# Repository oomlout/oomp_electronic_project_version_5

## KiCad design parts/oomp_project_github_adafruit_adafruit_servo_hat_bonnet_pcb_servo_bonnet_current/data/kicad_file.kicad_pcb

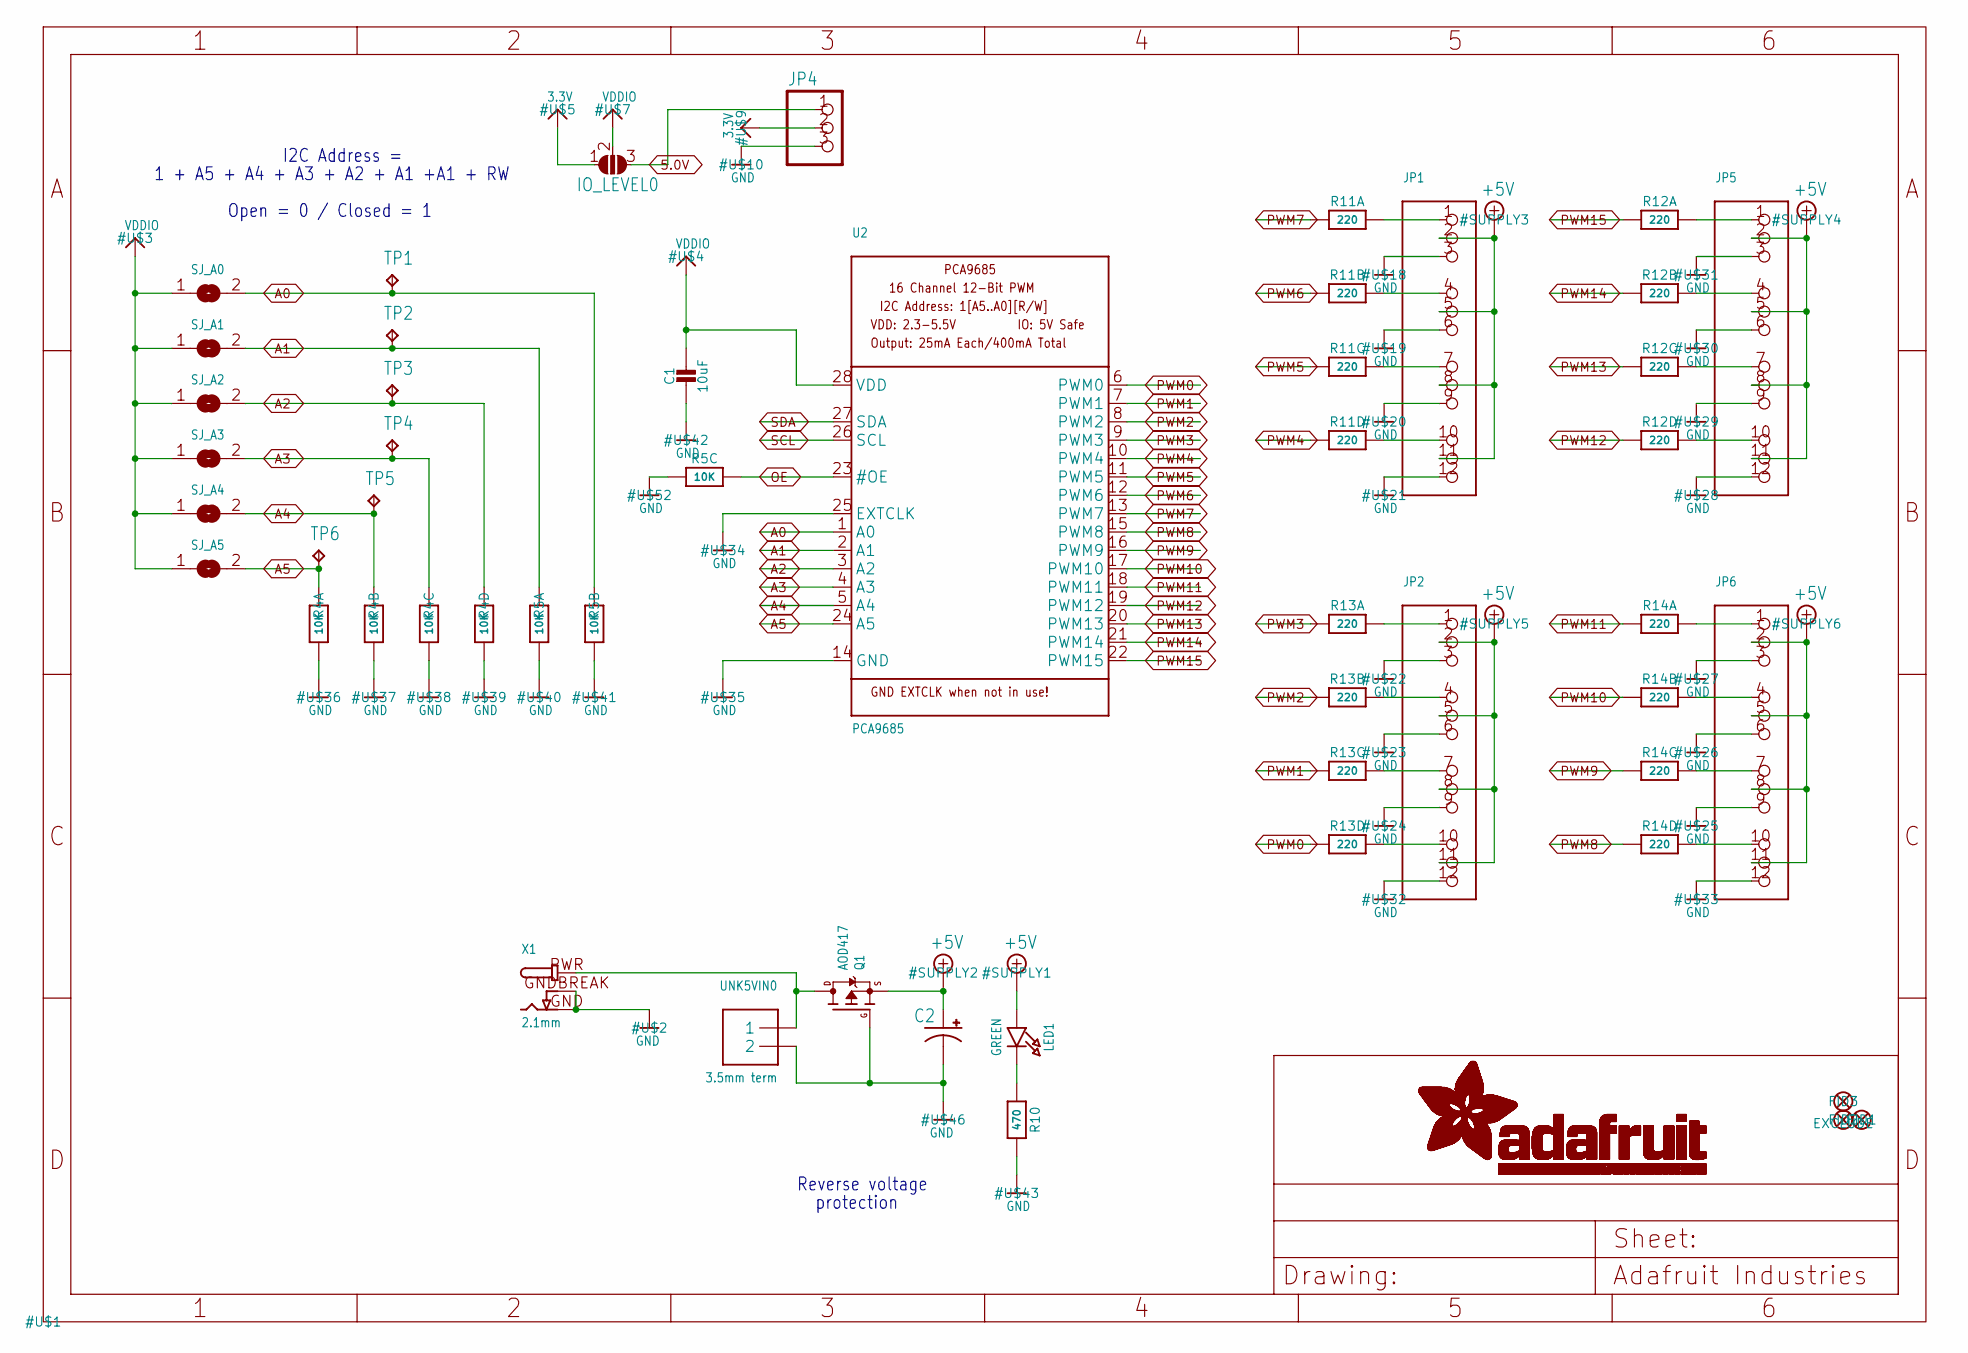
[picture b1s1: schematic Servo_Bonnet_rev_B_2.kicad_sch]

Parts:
C1: 10uF; 0805-NO
C2: CPOL-USE3.5-8; E3,5-8
FID1, FID2, FID3: FIDUCIAL_1MM
IO_LEVEL0: SOLDERJUMPER_2WAY; SOLDERJUMPER_2WAY_OPEN_NOPASTE
JP1, JP2, JP5, JP6: HEADER-3X04; 3X04
JP4: HEADER-1X3ROUND; 1X03_ROUND
LED1: GREEN; CHIPLED_0805_NOOUTLINE
Q1: AOD417; TO252
R4, R5: 10K; RESPACK_4X0603
R10: 470; 0603-NO
R11, R12, R13, R14: 220; RESPACK_4X0603
SJ_A0, SJ_A1, SJ_A2, SJ_A3, SJ_A4, SJ_A5: SOLDERJUMPERREFLOW_NOPASTE; SOLDERJUMPER_REFLOW_NOPASTE
TP1, TP2, TP3, TP4, TP5, TP6: TPB1,27; B1,27
U2: PCA9685; TSSOP28
UNK5VIN0: 3.5mm term; TERMBLOCK_1X2-3.5MM
X1: 2.1mm; DCJACK_2MM_PTH

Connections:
3.3V: IO_LEVEL0.1, JP4.2; also elsewhere on the board
5.0V: IO_LEVEL0.3, JP4.1; also elsewhere on the board
+5V: C2.+, JP1.2, JP1.5, JP1.8, JP1.11, JP2.2, JP2.5, JP2.8, JP2.11, JP5.2, JP5.5, JP5.8, JP5.11, JP6.2, JP6.5, JP6.8, JP6.11, LED1.A, Q1.2 (S)
A0: R5.7 (2), SJ_A0.2, TP1.TP, U2.1 (A0)
A1: R5.8 (2), SJ_A1.2, TP2.TP, U2.2 (A1)
A2: R4.5 (2), SJ_A2.2, TP3.TP, U2.3 (A2)
A3: R4.6 (2), SJ_A3.2, TP4.TP, U2.4 (A3)
A4: R4.7 (2), SJ_A4.2, TP5.TP, U2.5 (A4)
A5: R4.8 (2), SJ_A5.2, TP6.TP, U2.24 (A5)
GND: C1.2, C2.-, JP1.3, JP1.6, JP1.9, JP1.12, JP2.3, JP2.6, JP2.9, JP2.12, JP4.3, JP5.3, JP5.6, JP5.9, JP5.12, JP6.3, JP6.6, JP6.9, JP6.12, Q1.1 (G), R4.1, R4.2 (1), R4.3 (1), R4.4 (1), R5.1, R5.2 (1), R5.6 (2), R10.2, U2.14 (GND), U2.25 (EXTCLK), UNK5VIN0.2, X1.GND, X1.GNDBREAK; also elsewhere on the board
unnamed: LED1.C, R10.1
unnamed: JP1.4, R11.7 (2)
unnamed: JP1.1, R11.8 (2)
unnamed: JP1.7, R11.6 (2)
unnamed: JP1.10, R11.5 (2)
unnamed: JP2.1, R13.8 (2)
unnamed: JP2.4, R13.7 (2)
unnamed: JP2.7, R13.6 (2)
unnamed: JP2.10, R13.5 (2)
unnamed: JP6.10, R14.5 (2)
unnamed: JP6.7, R14.6 (2)
unnamed: JP6.4, R14.7 (2)
unnamed: JP6.1, R14.8 (2)
unnamed: JP5.10, R12.5 (2)
unnamed: JP5.7, R12.6 (2)
unnamed: JP5.4, R12.7 (2)
unnamed: JP5.1, R12.8 (2)
OE: R5.3 (1), U2.23 (#OE)
PWM0: R13.4 (1), U2.6 (PWM0)
PWM1: R13.3 (1), U2.7 (PWM1)
PWM2: R13.2 (1), U2.8 (PWM2)
PWM3: R13.1, U2.9 (PWM3)
PWM4: R11.4 (1), U2.10 (PWM4)
PWM5: R11.3 (1), U2.11 (PWM5)
PWM6: R11.2 (1), U2.12 (PWM6)
PWM7: R11.1, U2.13 (PWM7)
PWM8: R14.4 (1), U2.15 (PWM8)
PWM9: R14.3 (1), U2.16 (PWM9)
PWM10: R14.2 (1), U2.17 (PWM10)
PWM11: R14.1, U2.18 (PWM11)
PWM12: R12.4 (1), U2.19 (PWM12)
PWM13: R12.3 (1), U2.20 (PWM13)
PWM14: R12.2 (1), U2.21 (PWM14)
PWM15: R12.1, U2.22 (PWM15)
PWR: Q1.3 (D), UNK5VIN0.1, X1.PWR
SCL: U2.26 (SCL); also elsewhere on the board
SDA: U2.27 (SDA); also elsewhere on the board
VDDIO: C1.1, IO_LEVEL0.2, SJ_A0.1, SJ_A1.1, SJ_A2.1, SJ_A3.1, SJ_A4.1, SJ_A5.1, U2.28 (VDD)

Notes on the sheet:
protection
Open = 0 / Closed = 1
1 + A5 + A4 + A3 + A2 + A1 +A1 + RW
I2C Address =
Reverse voltage

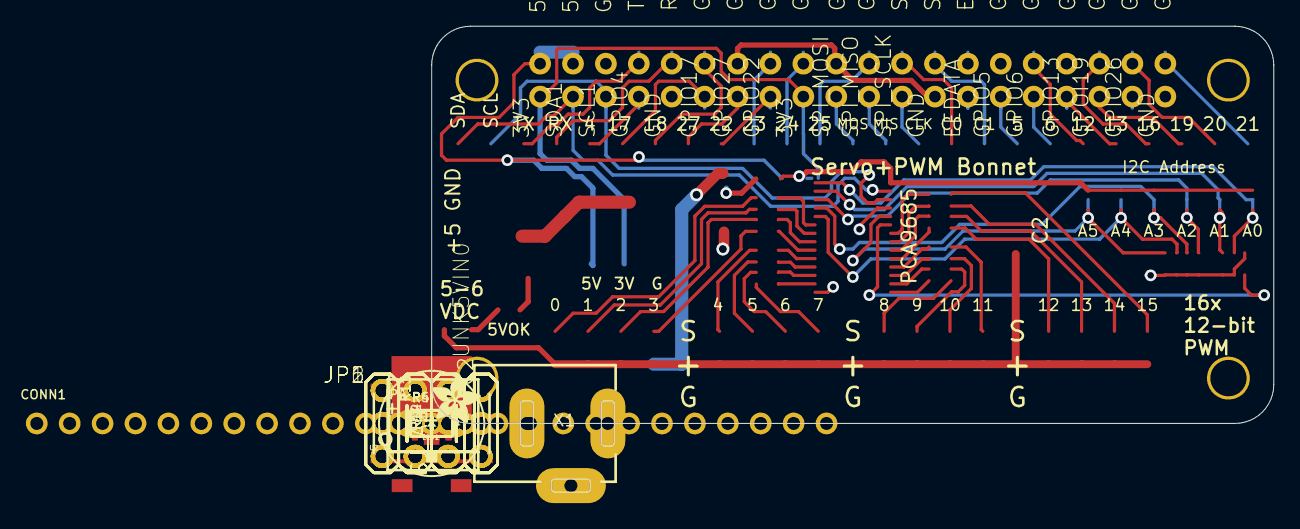
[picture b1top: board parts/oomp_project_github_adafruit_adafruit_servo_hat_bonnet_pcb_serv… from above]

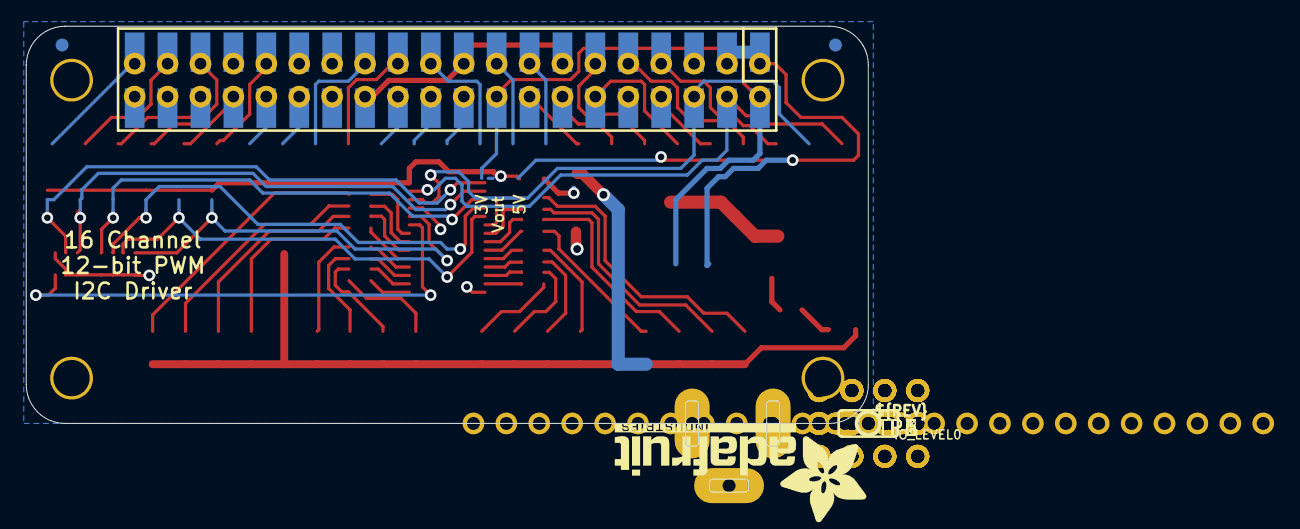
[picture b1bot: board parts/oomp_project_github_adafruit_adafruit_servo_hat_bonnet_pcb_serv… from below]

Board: 2 copper layers, 65.0 x 30.7 mm, 40 parts (9 on the bottom side), 74 nets.

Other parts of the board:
CONN1: HEADER-1X25; 1X25_ROUND_70MIL
RPI1: RASPBERRYPI_BPLUS_BONNET_THMSMT; PI_BONNET_THMSMT
U$6: ADAFRUIT_TEXT_20MM
U$8: ADAFRUIT_3.5MM
U$11: PCBFEAT-REV-040

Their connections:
3.3V: RPI1.1, RPI1.17, RPI1.S1, RPI1.S17; also elsewhere on the board
5.0V: RPI1.2, RPI1.4, RPI1.S2, RPI1.S4; also elsewhere on the board
EECLK: RPI1.28, RPI1.S28
EEDATA: RPI1.27, RPI1.S27
GND: RPI1.6, RPI1.9, RPI1.14, RPI1.20, RPI1.25, RPI1.30, RPI1.34, RPI1.39, RPI1.S6, RPI1.S9, RPI1.S14, RPI1.S20, RPI1.S25, RPI1.S30, RPI1.S34, RPI1.S39; also elsewhere on the board
GPIO4: CONN1.5, RPI1.7, RPI1.S7
GPIO5: CONN1.18, RPI1.29, RPI1.S29
GPIO6: CONN1.19, RPI1.31, RPI1.S31
GPIO12: CONN1.20, RPI1.32, RPI1.S32
GPIO13: CONN1.21, RPI1.33, RPI1.S33
GPIO16: CONN1.22, RPI1.36, RPI1.S36
GPIO17: CONN1.6, RPI1.11, RPI1.S11
GPIO18: CONN1.7, RPI1.12, RPI1.S12
GPIO19: CONN1.23, RPI1.35, RPI1.S35
GPIO20: CONN1.24, RPI1.38, RPI1.S38
GPIO21: CONN1.25, RPI1.40, RPI1.S40
GPIO22: CONN1.9, RPI1.15, RPI1.S15
GPIO23: CONN1.10, RPI1.16, RPI1.S16
GPIO24: CONN1.11, RPI1.18, RPI1.S18
GPIO25: CONN1.12, RPI1.22, RPI1.S22
GPIO26: RPI1.37, RPI1.S37
GPIO27: CONN1.8, RPI1.13, RPI1.S13
RXD: CONN1.4, RPI1.10, RPI1.S10
SCL: CONN1.2, RPI1.5, RPI1.S5; also elsewhere on the board
SDA: CONN1.1, RPI1.3, RPI1.S3; also elsewhere on the board
SPI_CE0: CONN1.16, RPI1.24, RPI1.S24
SPI_CE1: CONN1.17, RPI1.26, RPI1.S26
SPI_MISO: CONN1.14, RPI1.21, RPI1.S21
SPI_MOSI: CONN1.13, RPI1.19, RPI1.S19
SPI_SCLK: CONN1.15, RPI1.23, RPI1.S23
TXD: CONN1.3, RPI1.8, RPI1.S8

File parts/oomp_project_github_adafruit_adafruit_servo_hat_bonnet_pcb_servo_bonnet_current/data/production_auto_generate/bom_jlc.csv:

Comment,Designator,Footprint,LCSC Part #
,JP4,Servo Bonnet rev B-import-fps:1X03_ROUND,C49257
,"JP1,JP2,JP5,JP6",Servo Bonnet rev B-import-fps:3X04,
,U$8,Servo Bonnet rev B-import-fps:ADAFRUIT_3.5MM,
,U$6,Servo Bonnet rev B-import-fps:ADAFRUIT_TEXT_20MM,
,C2,"Servo Bonnet rev B-import-fps:E3,5-8",
,U$11,Servo Bonnet rev B-import-fps:PCBFEAT-REV-040,
,IO_LEVEL0,Servo Bonnet rev B-import-fps:SOLDERJUMPER_2WAY_OPEN_NOPASTE,
10K,"R4,R5",Servo Bonnet rev B-import-fps:RESPACK_4X0603,C98220
10uF,C1,Servo Bonnet rev B-import-fps:0805-NO,
2.1mm,X1,Servo Bonnet rev B-import-fps:DCJACK_2MM_PTH,
220,"R11,R12,R13,R14",Servo Bonnet rev B-import-fps:RESPACK_4X0603,C2907127
3.5mm term,UNK5VIN0,Servo Bonnet rev B-import-fps:TERMBLOCK_1X2-3.5MM,
470,R10,Servo Bonnet rev B-import-fps:0603-NO,C23179
AOD417,Q1,Servo Bonnet rev B-import-fps:TO252,
GREEN,LED1,Servo Bonnet rev B-import-fps:CHIPLED_0805_NOOUTLINE,
HEADER-1X25,CONN1,Servo Bonnet rev B-import-fps:1X25_ROUND_70MIL,C2883713
PCA9685,U2,Servo Bonnet rev B-import-fps:TSSOP28,
RASPBERRYPI_BPLUS_BONNET_THMSMT,RPI1,Servo Bonnet rev B-import-fps:PI_BONNET_THMSMT,
"TPB1,27","TP1,TP2,TP3,TP4,TP5,TP6","Servo Bonnet rev B-import-fps:B1,27",

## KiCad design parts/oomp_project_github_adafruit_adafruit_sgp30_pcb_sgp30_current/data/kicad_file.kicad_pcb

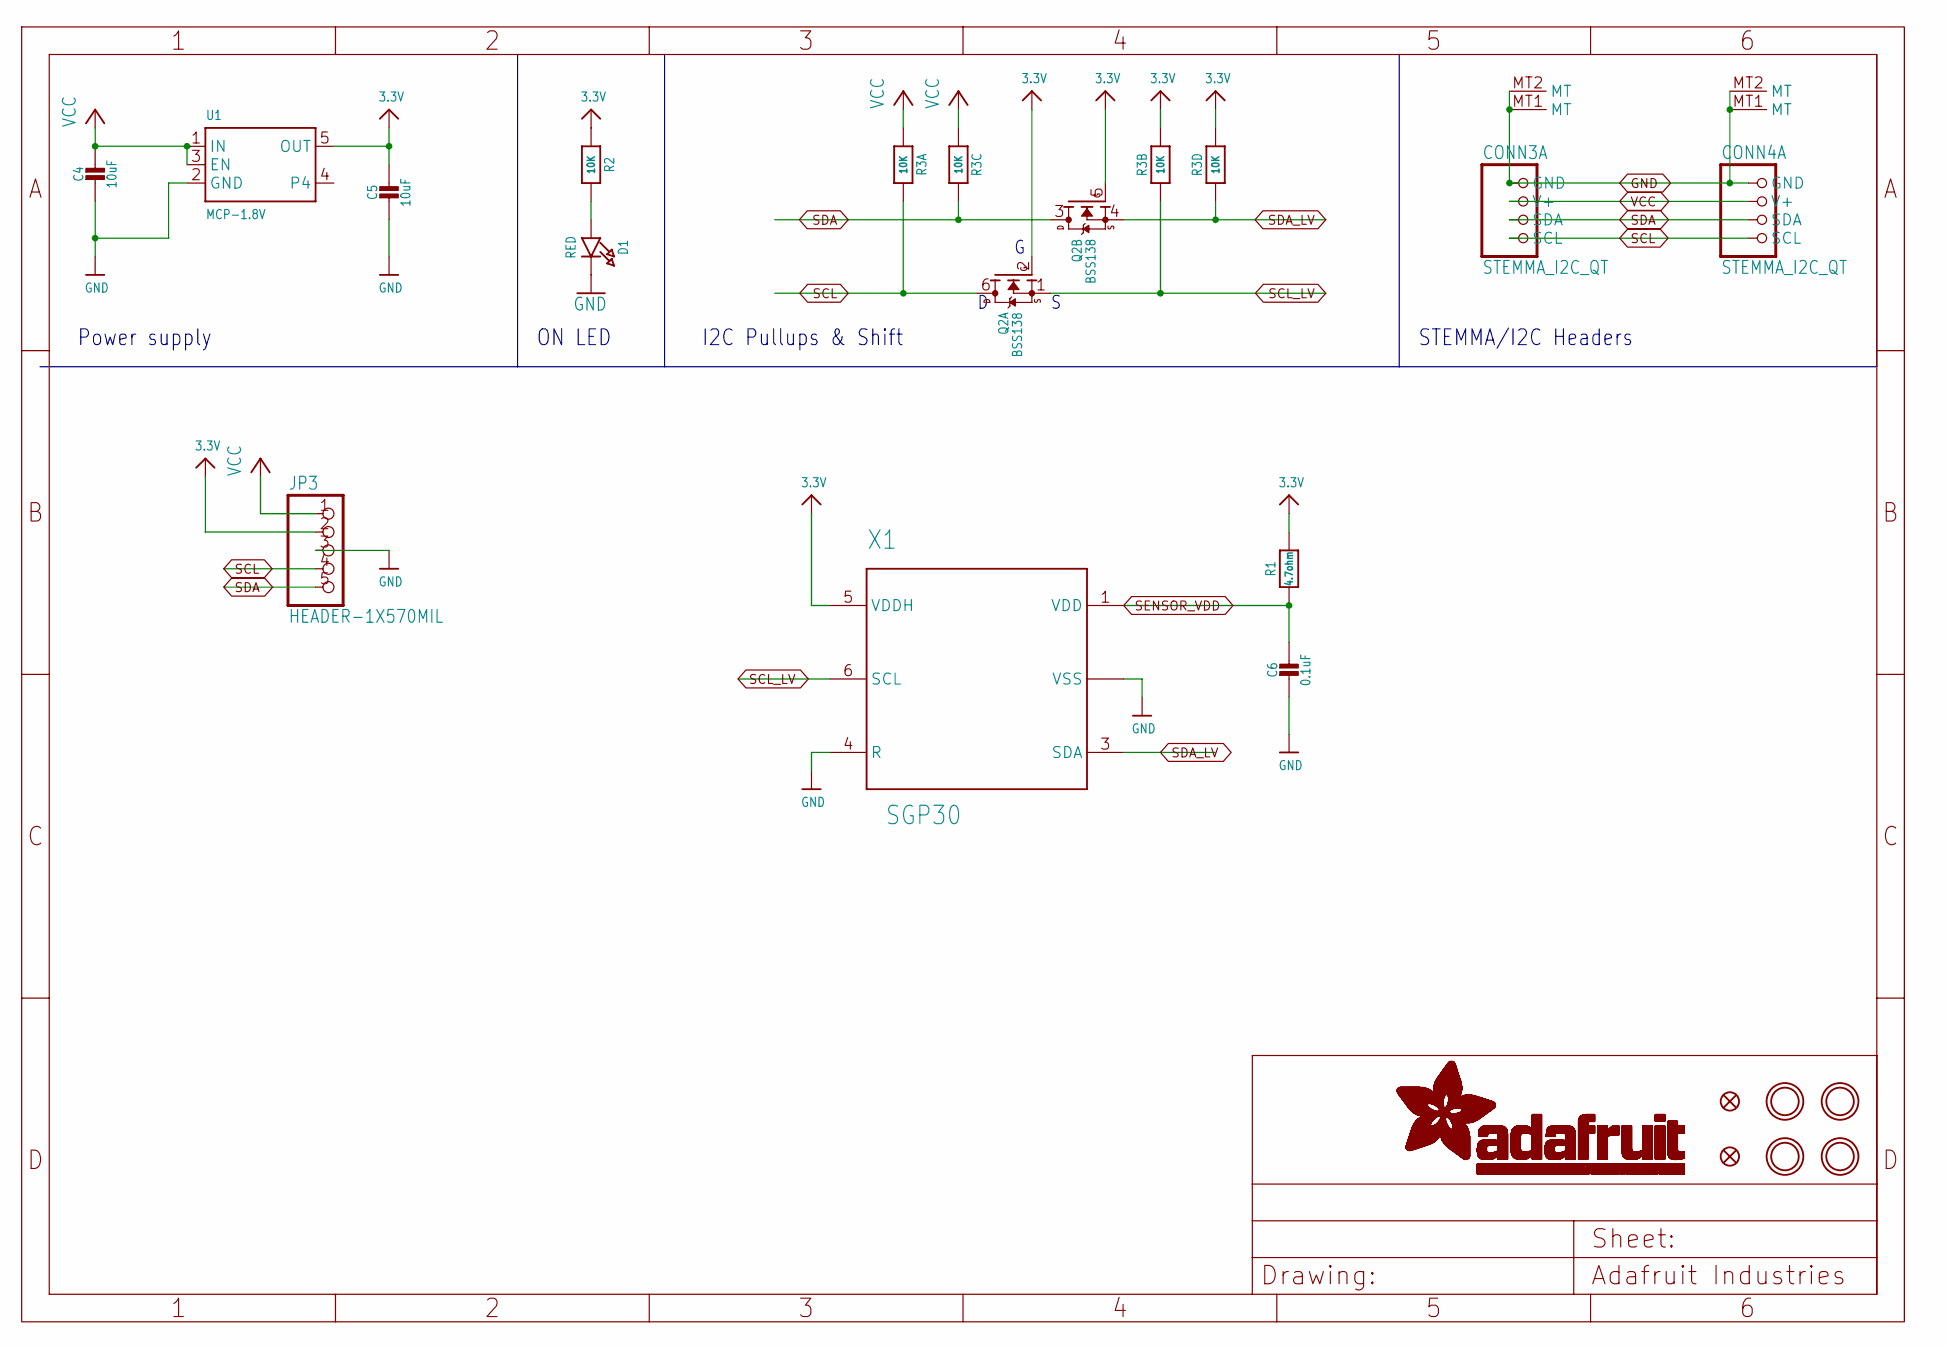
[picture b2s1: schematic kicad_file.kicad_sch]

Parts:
C4, C5: 10uF; 0805-NO
C6: 0.1uF; 0603-NO
CONN3, CONN4: STEMMA_I2C_QT; JST_SH4
D1: RED; CHIPLED_0603_NOOUTLINE
FID3, FID4: FIDUCIAL_1MM
JP3: HEADER-1X570MIL; 1X05_ROUND_70
Q2: BSS138; SOT363
R1: 4.7ohm; 0603-NO
R2: 10K; 0603-NO
R3: 10K; RESPACK_4X0603
U1: MCP-1.8V; SOT23-5
U$28, U$29, U$31, U$32: MOUNTINGHOLE2.5; MOUNTINGHOLE_2.5_PLATED
X1: SGP30

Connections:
3.3V: C5.1, JP3.2, Q2.2 (G), Q2.5 (G), R1.2, R2.1, R3.2 (1), R3.4 (1), U1.5 (OUT), X1.5 (VDDH)
GND: C4.2, C5.2, C6.2, CONN3.1 (GND), CONN3.MT1 (MT), CONN3.MT2 (MT), CONN4.1 (GND), CONN4.MT1 (MT), CONN4.MT2 (MT), D1.C, JP3.3, U1.2 (GND), X1.2 (VSS), X1.4 (R), X1.P$7 (VSS)
unnamed: D1.A, R2.2
SCL: CONN3.4 (SCL), CONN4.4 (SCL), JP3.4, Q2.6 (D), R3.8 (2)
SCL_LV: Q2.1 (S), R3.7 (2), X1.6 (SCL)
SDA: CONN3.3 (SDA), CONN4.3 (SDA), JP3.5, Q2.3 (D), R3.6 (2)
SDA_LV: Q2.4 (S), R3.5 (2), X1.3 (SDA)
SENSOR_VDD: C6.1, R1.1, X1.1 (VDD)
VCC: C4.1, CONN3.2 (V+), CONN4.2 (V+), JP3.1, R3.1, R3.3 (1), U1.1 (IN), U1.3 (EN)

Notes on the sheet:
I2C Pullups & Shift
Power supply
ON LED
STEMMA/I2C Headers

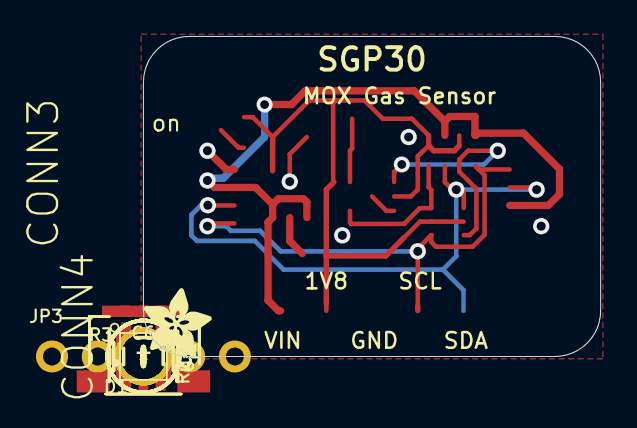
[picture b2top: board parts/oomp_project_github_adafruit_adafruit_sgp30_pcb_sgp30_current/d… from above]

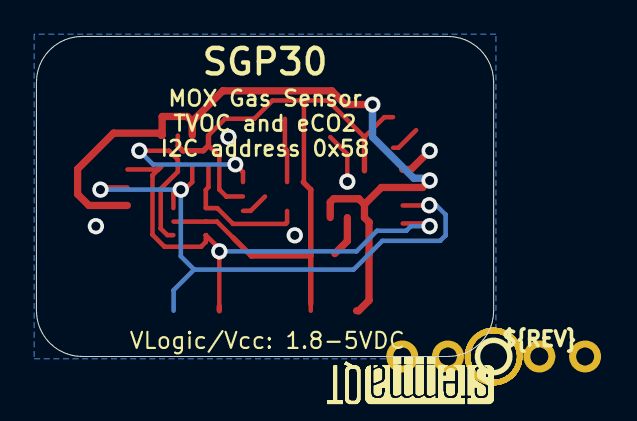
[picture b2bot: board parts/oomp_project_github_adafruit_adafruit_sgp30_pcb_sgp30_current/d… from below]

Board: 2 copper layers, 25.4 x 17.8 mm, 23 parts (3 on the bottom side), 9 nets.

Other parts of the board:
U$34: ADAFRUIT_3.5MM
U$35: PCBFEAT-REV-040
U$36, U$37: STEMMAQT

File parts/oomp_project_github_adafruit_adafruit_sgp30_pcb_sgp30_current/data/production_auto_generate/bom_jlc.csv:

Comment,Designator,Footprint,LCSC Part #
,JP3,SGP30 Rev D-import-fps:1X05_ROUND_70,C42431835
,U$34,SGP30 Rev D-import-fps:ADAFRUIT_3.5MM,
,U$35,SGP30 Rev D-import-fps:PCBFEAT-REV-040,
,"U$36,U$37",SGP30 Rev D-import-fps:STEMMAQT,
0.1uF,C6,SGP30 Rev D-import-fps:0603-NO,C14663
10K,R2,SGP30 Rev D-import-fps:0603-NO,C98220
10K,R3,SGP30 Rev D-import-fps:RESPACK_4X0603,C98220
10uF,"C4,C5",SGP30 Rev D-import-fps:0805-NO,
4.7ohm,R1,SGP30 Rev D-import-fps:0603-NO,
BSS138,Q2,SGP30 Rev D-import-fps:SOT363,
MCP-1.8V,U1,SGP30 Rev D-import-fps:SOT23-5,
RED,D1,SGP30 Rev D-import-fps:CHIPLED_0603_NOOUTLINE,
SGP30,X1,SGP30 Rev D-import-fps:SGP30,
STEMMA_I2C_QT,"CONN3,CONN4",SGP30 Rev D-import-fps:JST_SH4,C160404

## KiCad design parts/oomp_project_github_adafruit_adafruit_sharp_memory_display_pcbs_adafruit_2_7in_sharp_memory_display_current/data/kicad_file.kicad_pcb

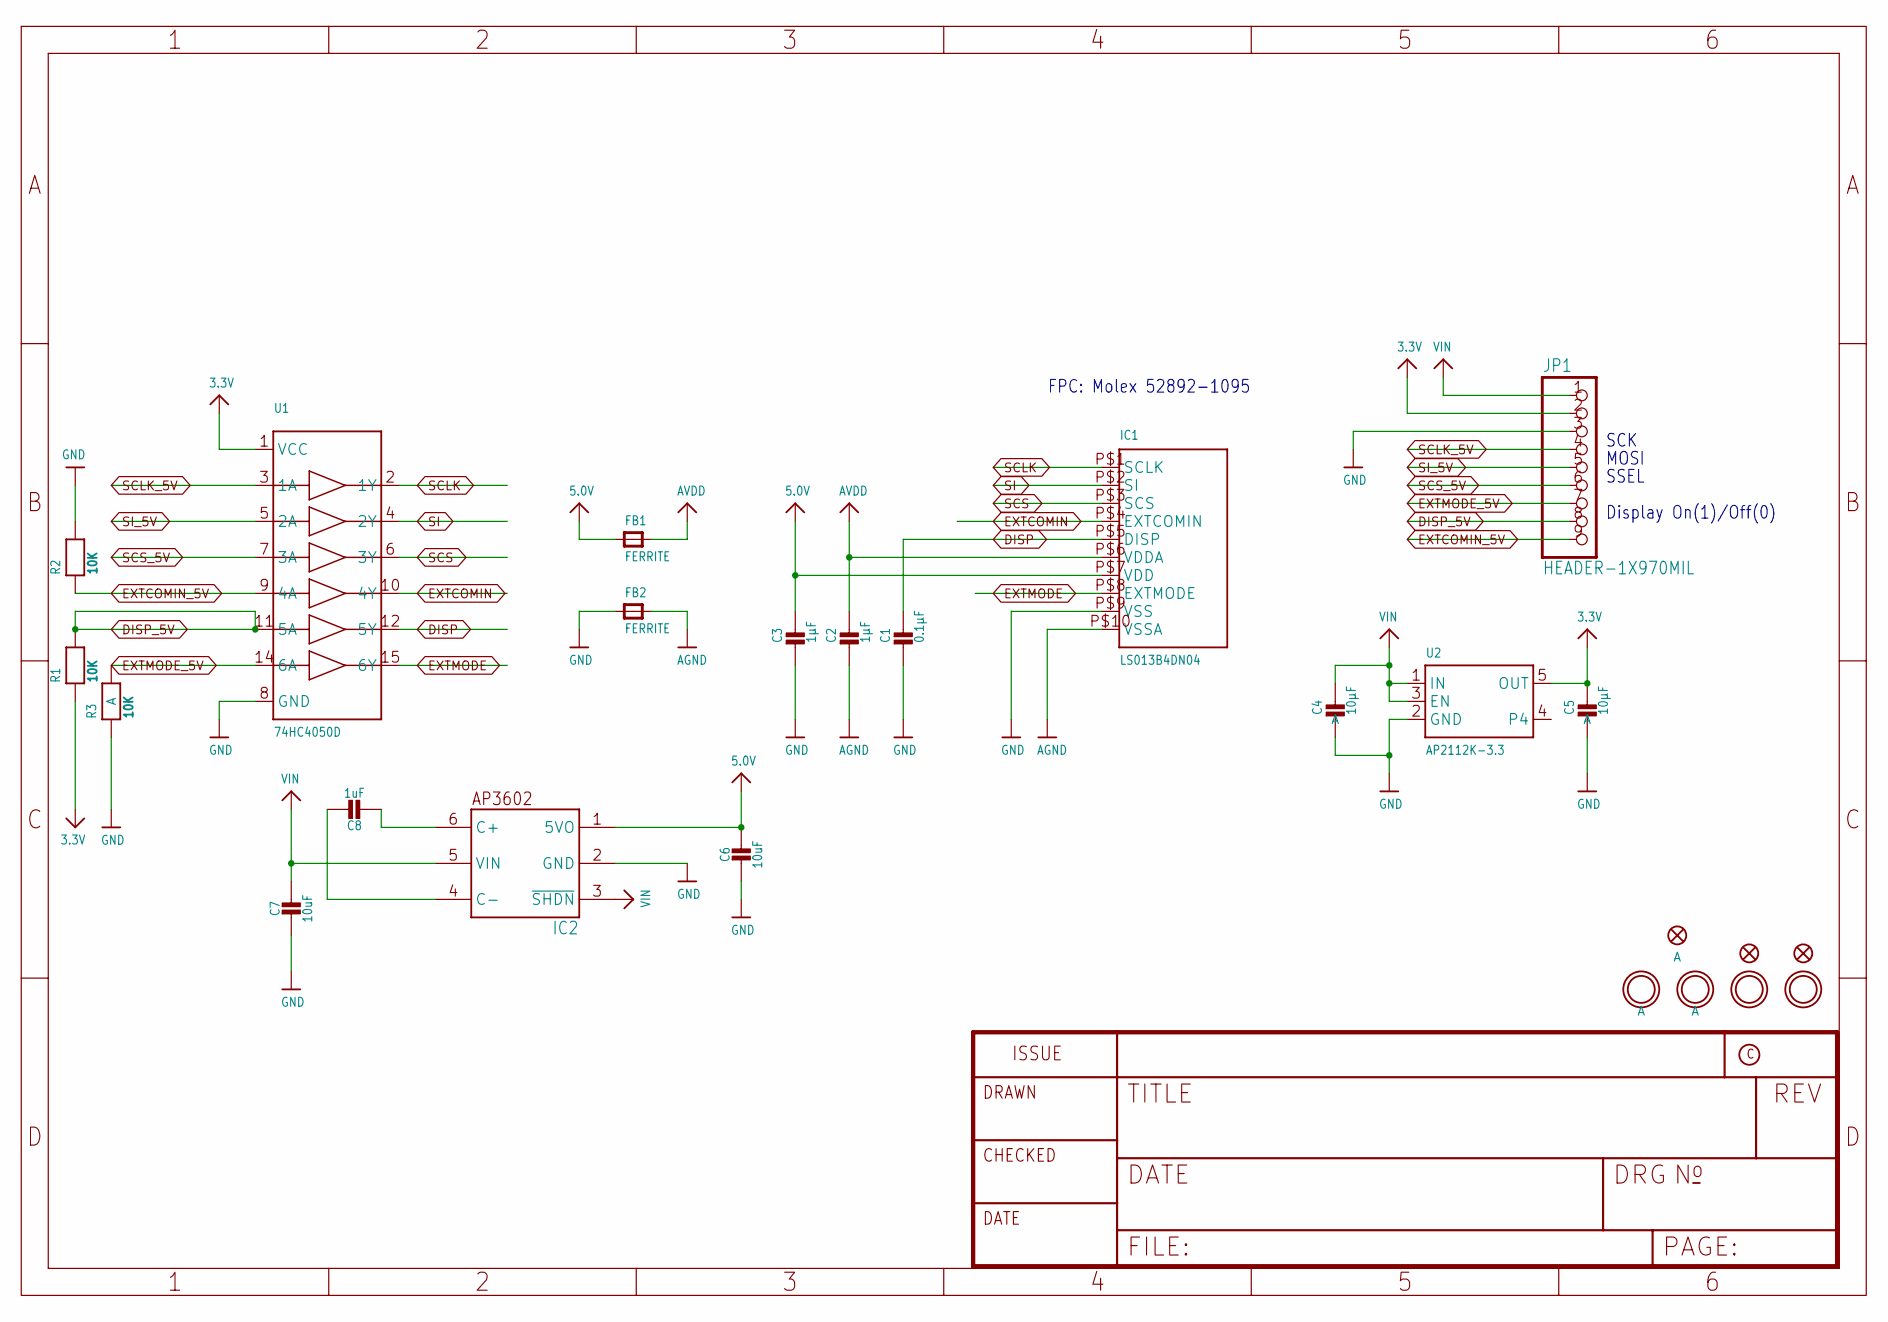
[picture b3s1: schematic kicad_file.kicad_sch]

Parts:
C1: 0.1µF; 0603-NO
C2: 1µF; 0805_10MGAP
C3: 1µF; 0805-NO
C4, C5: 10µF; 0805-NO
C6, C7: 10uF; 0805-NO
C8: 1uF; 0805-NO
FB1, FB2: FERRITE; _0805
FID1, FID2, FID3: FIDUCIAL_1MM
IC1: LS013B4DN04; SHARP_2.7IN
IC2: AP3602; SOT23-6
JP1: HEADER-1X970MIL; 1X09_ROUND_70
R1, R2, R3: 10K; 0603-NO
U1: 74HC4050D; SOIC16
U2: AP2112K-3.3; SOT23-5
U$21, U$22: MOUNTINGHOLE2.5_THICK; MOUNTINGHOLE_2.5_PLATED_THICK
U$27, U$28: MOUNTINGHOLE2.5; MOUNTINGHOLE_2.5_PLATED

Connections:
3.3V: C5.1, JP1.2, R1.1, U1.1 (VCC), U2.5 (OUT)
5.0V: C3.1, C6.1, FB1.1, IC1.P$7 (VDD), IC2.1 (5VO)
AGND: C2.2, FB2.2, IC1.P$10 (VSSA)
AVDD: C2.1, FB1.2, IC1.P$6 (VDDA)
DISP: C1.1, IC1.P$5 (DISP), U1.12 (5Y)
DISP_5V: JP1.8, R1.2, U1.11 (5A)
EXTCOMIN: IC1.P$4 (EXTCOMIN), U1.10 (4Y)
EXTCOMIN_5V: JP1.9, R2.1, U1.9 (4A)
EXTMODE: IC1.P$8 (EXTMODE), U1.15 (6Y)
EXTMODE_5V: JP1.7, R3.2, U1.14 (6A)
GND: C1.2, C3.2, C4.2, C5.2, C6.2, C7.2, FB2.1, IC1.P$9 (VSS), IC2.2 (GND), JP1.3, R2.2, R3.1, U1.8 (GND), U2.2 (GND)
unnamed: C8.2, IC2.6 (C+)
unnamed: C8.1, IC2.4 (C-)
SCLK: IC1.P$1 (SCLK), U1.2 (1Y)
SCLK_5V: JP1.4, U1.3 (1A)
SCS: IC1.P$3 (SCS), U1.6 (3Y)
SCS_5V: JP1.6, U1.7 (3A)
SI: IC1.P$2 (SI), U1.4 (2Y)
SI_5V: JP1.5, U1.5 (2A)
VIN: C4.1, C7.1, IC2.3 (~SHDN), IC2.5 (VIN), JP1.1, U2.1 (IN), U2.3 (EN)

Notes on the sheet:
SCK
Display On(1)/Off(0)
MOSI
SSEL
FPC: Molex 52892-1095

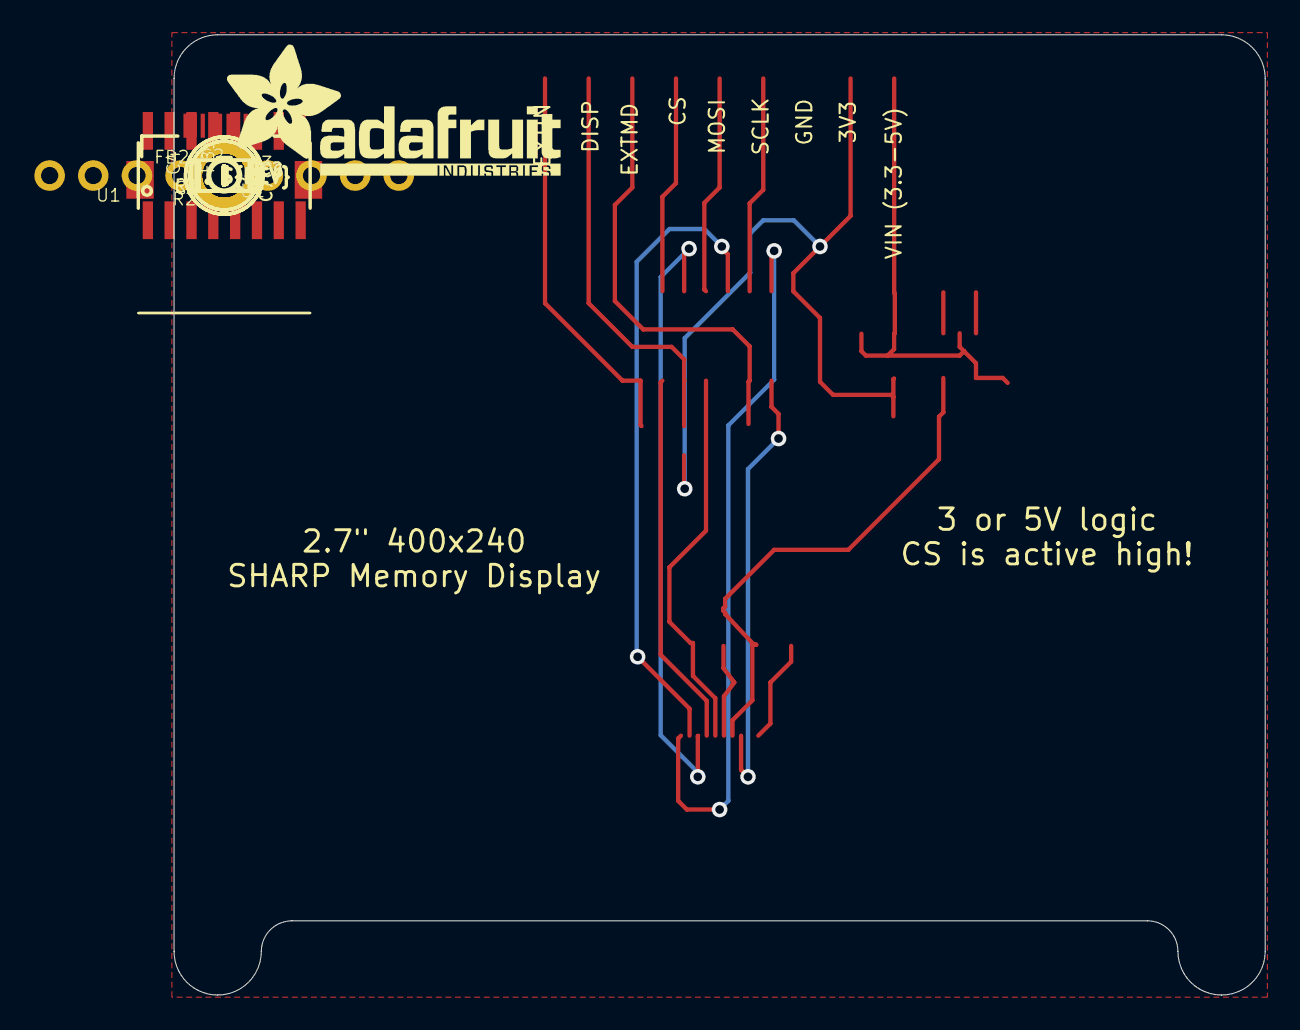
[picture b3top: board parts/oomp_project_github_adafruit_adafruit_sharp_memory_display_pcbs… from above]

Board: 16 copper layers, 63.5 x 55.9 mm, 27 parts (0 on the bottom side), 20 nets.

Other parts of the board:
U$29: PCBFEAT-REV-040
U$32: ADAFRUIT_TEXT_20MM

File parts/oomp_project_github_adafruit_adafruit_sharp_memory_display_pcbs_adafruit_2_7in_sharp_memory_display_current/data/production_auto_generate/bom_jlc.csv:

Comment,Designator,Footprint,LCSC Part #
,JP1,Adafruit 2.7in Sharp Memory Display-import-fps:1X09_ROUND_70,C2932701
,U$32,Adafruit 2.7in Sharp Memory Display-import-fps:ADAFRUIT_TEXT_20MM,
,U$29,Adafruit 2.7in Sharp Memory Display-import-fps:PCBFEAT-REV-040,
0.1µF,C1,Adafruit 2.7in Sharp Memory Display-import-fps:0603-NO,C14663
10K,"R1,R2,R3",Adafruit 2.7in Sharp Memory Display-import-fps:0603-NO,C98220
10uF,"C6,C7",Adafruit 2.7in Sharp Memory Display-import-fps:0805-NO,
10µF,"C4,C5",Adafruit 2.7in Sharp Memory Display-import-fps:0805-NO,
1uF,C8,Adafruit 2.7in Sharp Memory Display-import-fps:0805-NO,
1µF,C3,Adafruit 2.7in Sharp Memory Display-import-fps:0805-NO,
1µF,C2,Adafruit 2.7in Sharp Memory Display-import-fps:0805_10MGAP,
74HC4050D,U1,Adafruit 2.7in Sharp Memory Display-import-fps:SOIC16,
AP2112K-3.3,U2,Adafruit 2.7in Sharp Memory Display-import-fps:SOT23-5,
AP3602,IC2,Adafruit 2.7in Sharp Memory Display-import-fps:SOT23-6,
FERRITE,"FB1,FB2",Adafruit 2.7in Sharp Memory Display-import-fps:_0805,
LS013B4DN04,IC1,Adafruit 2.7in Sharp Memory Display-import-fps:SHARP_2.7IN,

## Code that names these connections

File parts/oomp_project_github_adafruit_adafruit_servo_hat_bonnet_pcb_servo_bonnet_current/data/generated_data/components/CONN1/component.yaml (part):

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      position:
        x: 193.04
        y: 83.82
      net: GPIO4
      net_aliases:
      - GPIO4
      net_scope: global
      no_connect: false
      connected_to:
      - reference: RPI1
        pin_number: '7'
        pin_name: GPIO4
      - reference: RPI1
        pin_number: S7
        pin_name: GPIO4
    - number: '6'
      name: '6'
      electrical_type: passive
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      position:
        x: 193.04
        y: 86.36
      net: GPIO17
      net_aliases:
      - GPIO17
      net_scope: global
      no_connect: false
      connected_to:
      - reference: RPI1
        pin_number: '11'
        pin_name: GPIO17
      - reference: RPI1
        pin_number: S11
        pin_name: GPIO17
    - number: '7'
      name: '7'
      electrical_type: passive
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      position:
        x: 193.04
        y: 88.9
      net: GPIO18
      net_aliases:
      - GPIO18
      net_scope: global
      no_connect: false
      connected_to:
      - reference: RPI1
        pin_number: '12'
        pin_name: GPIO18
      - reference: RPI1
        pin_number: S12
        pin_name: GPIO18
    - number: '8'
      name: '8'
      electrical_type: passive
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      position:
        x: 193.04
        y: 91.44
      net: GPIO27
      net_aliases:
      - GPIO27
      net_scope: global
      no_connect: false
      connected_to:
      - reference: RPI1
        pin_number: '13'
        pin_name: GPIO27
      - reference: RPI1
        pin_number: S13
        pin_name: GPIO27
    - number: '9'
      name: '9'
      electrical_type: passive
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      position:
        x: 193.04
        y: 93.98
      net: GPIO22
      net_aliases:
      - GPIO22
      net_scope: global
      no_connect: false
      connected_to:
      - reference: RPI1
        pin_number: '15'
        pin_name: GPIO22
      - reference: RPI1
        pin_number: S15
        pin_name: GPIO22
    - number: '10'
      name: '10'
      electrical_type: passive
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      position:
        x: 193.04
        y: 96.52
      net: GPIO23
      net_aliases:
      - GPIO23
      net_scope: global
      no_connect: false
      connected_to:
      - reference: RPI1
        pin_number: '16'
        pin_name: GPIO23
      - reference: RPI1
        pin_number: S16
        pin_name: GPIO23
    - number: '11'
      name: '11'
      electrical_type: passive
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      position:
        x: 193.04
        y: 99.06
      net: GPIO24
      net_aliases:
      - GPIO24
      net_scope: global
      no_connect: false
      connected_to:
      - reference: RPI1
        pin_number: '18'
        pin_name: GPIO24
      - reference: RPI1
        pin_number: S18
        pin_name: GPIO24
    - number: '12'
      name: '12'
      electrical_type: passive
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      position:
        x: 193.04
        y: 101.6
      net: GPIO25
      net_aliases:
      - GPIO25
      net_scope: global
      no_connect: false
      connected_to:
      - reference: RPI1
        pin_number: '22'
        pin_name: GPIO25
      - reference: RPI1
        pin_number: S22
        pin_name: GPIO25
    - number: '13'
      name: '13'
      electrical_type: passive
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      connected_to:
      - reference: RPI1
        pin_number: '19'
        pin_name: SPI_MOSI
      - reference: RPI1
        pin_number: S19
        pin_name: SPI_MOSI
    - number: '14'
      name: '14'
      electrical_type: passive
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      connected_to:
      - reference: RPI1
        pin_number: '21'
        pin_name: SPI_MISO
      - reference: RPI1
        pin_number: S21
        pin_name: SPI_MISO
    - number: '15'
      name: '15'
      electrical_type: passive
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      connected_to:
      - reference: RPI1
        pin_number: '23'
        pin_name: SPI_SCLK
      - reference: RPI1
        pin_number: S23
        pin_name: SPI_SCLK
    - number: '16'
      name: '16'
      electrical_type: passive
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      connected_to:
      - reference: RPI1
        pin_number: '24'
        pin_name: '#SPI_CE0'
      - reference: RPI1
        pin_number: S24
        pin_name: '#SPI_CE0'
    - number: '17'
      name: '17'
      electrical_type: passive
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      connected_to:
      - reference: RPI1
        pin_number: '26'
        pin_name: '#SPI_CE1'
      - reference: RPI1
        pin_number: S26
        pin_name: '#SPI_CE1'
    - number: '18'
      name: '18'
      electrical_type: passive
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      position:
        x: 193.04
        y: 116.84
      net: GPIO5
      net_aliases:
      - GPIO5
      net_scope: global
      no_connect: false
      connected_to:
      - reference: RPI1
        pin_number: '29'
        pin_name: GPIO5
      - reference: RPI1
        pin_number: S29
        pin_name: GPIO5
    - number: '19'
      name: '19'
      electrical_type: passive
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      position:
        x: 193.04
        y: 119.38
      net: GPIO6
      net_aliases:
      - GPIO6
      net_scope: global
      no_connect: false
      connected_to:
      - reference: RPI1
        pin_number: '31'
        pin_name: GPIO6
      - reference: RPI1
        pin_number: S31
        pin_name: GPIO6
    - number: '20'
      name: '20'
      electrical_type: passive
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      position:
        x: 193.04
        y: 121.92
      net: GPIO12
      net_aliases:
      - GPIO12
      net_scope: global
      no_connect: false
      connected_to:
      - reference: RPI1
        pin_number: '32'
        pin_name: GPIO12
      - reference: RPI1
        pin_number: S32
        pin_name: GPIO12
    - number: '21'
      name: '21'
      electrical_type: passive
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      position:
        x: 193.04
        y: 124.46
      net: GPIO13
      net_aliases:
      - GPIO13
      net_scope: global
      no_connect: false
      connected_to:
      - reference: RPI1
        pin_number: '33'
        pin_name: GPIO13
      - reference: RPI1
        pin_number: S33
        pin_name: GPIO13
    - number: '22'
      name: '22'
      electrical_type: passive
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      position:
        x: 193.04
        y: 127.0
      net: GPIO16
      net_aliases:
      - GPIO16
      net_scope: global
      no_connect: false
      connected_to:
      - reference: RPI1
        pin_number: '36'
        pin_name: GPIO16
      - reference: RPI1
        pin_number: S36
        pin_name: GPIO16
    - number: '23'
      name: '23'
      electrical_type: passive
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      position:
        x: 193.04
        y: 129.54
      net: GPIO19
      net_aliases:
      - GPIO19
      net_scope: global
      no_connect: false
      connected_to:
      - reference: RPI1
        pin_number: '35'
        pin_name: GPIO19
      - reference: RPI1
        pin_number: S35
        pin_name: GPIO19
    - number: '24'
      name: '24'
      electrical_type: passive
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      position:
        x: 193.04
        y: 132.08
      net: GPIO20
      net_aliases:
      - GPIO20
      net_scope: global
      no_connect: false
      connected_to:
      - reference: RPI1
        pin_number: '38'
        pin_name: GPIO20
      - reference: RPI1
        pin_number: S38
        pin_name: GPIO20
    - number: '25'
      name: '25'
      electrical_type: passive
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      position:
        x: 193.04
        y: 134.62
      net: GPIO21
      net_aliases:
      - GPIO21
      net_scope: global
      no_connect: false
      connected_to:
      - reference: RPI1
        pin_number: '40'
        pin_name: GPIO21
      - reference: RPI1
        pin_number: S40
        pin_name: GPIO21
    size:
      local_graphics:
        measurement: symbol graphics only; excludes pins, properties, and text
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    pin_name: RXD
  - reference: RPI1
    pin_number: '11'
    pin_name: GPIO17
  - reference: RPI1
    pin_number: '12'
    pin_name: GPIO18
  - reference: RPI1
    pin_number: '13'
    pin_name: GPIO27
  - reference: RPI1
    pin_number: '15'
    pin_name: GPIO22
  - reference: RPI1
    pin_number: '16'
    pin_name: GPIO23
  - reference: RPI1
    pin_number: '18'
    pin_name: GPIO24
  - reference: RPI1
    pin_number: '19'
    pin_name: SPI_MOSI
  - reference: RPI1
    pin_number: '21'
    pin_name: SPI_MISO
  - reference: RPI1
    pin_number: '22'
    pin_name: GPIO25
  - reference: RPI1
    pin_number: '23'
    pin_name: SPI_SCLK
  - reference: RPI1
    pin_number: '24'
    pin_name: '#SPI_CE0'
  - reference: RPI1
    pin_number: '26'
    pin_name: '#SPI_CE1'
  - reference: RPI1
    pin_number: '29'
    pin_name: GPIO5
  - reference: RPI1
    pin_number: '3'
    pin_name: SDA
  - reference: RPI1
    pin_number: '31'
    pin_name: GPIO6
  - reference: RPI1
    pin_number: '32'
    pin_name: GPIO12
  - reference: RPI1
    pin_number: '33'
    pin_name: GPIO13
  - reference: RPI1
    pin_number: '35'
    pin_name: GPIO19
  - reference: RPI1
    pin_number: '36'
    pin_name: GPIO16
  - reference: RPI1
    pin_number: '38'
    pin_name: GPIO20
  - reference: RPI1
    pin_number: '40'
    pin_name: GPIO21
  - reference: RPI1
    pin_number: '5'
    pin_name: SCL
  - reference: RPI1
    pin_number: '7'
    pin_name: GPIO4
  - reference: RPI1
    pin_number: '8'
    pin_name: TXD
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    pin_name: RXD
  - reference: RPI1
    pin_number: S11
    pin_name: GPIO17
  - reference: RPI1
    pin_number: S12
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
